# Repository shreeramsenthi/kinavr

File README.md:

kinavr
=======================================================================================

Hardware and firmware for automated approach to the recording of animal kinematics using inertial measurement units and AVR microcontrollers.

The schematics and board layouts for the modular data loggers can be found in the `board_design` subdirectory.
The source code for the firmware for data loggers make up the rest of the repository.

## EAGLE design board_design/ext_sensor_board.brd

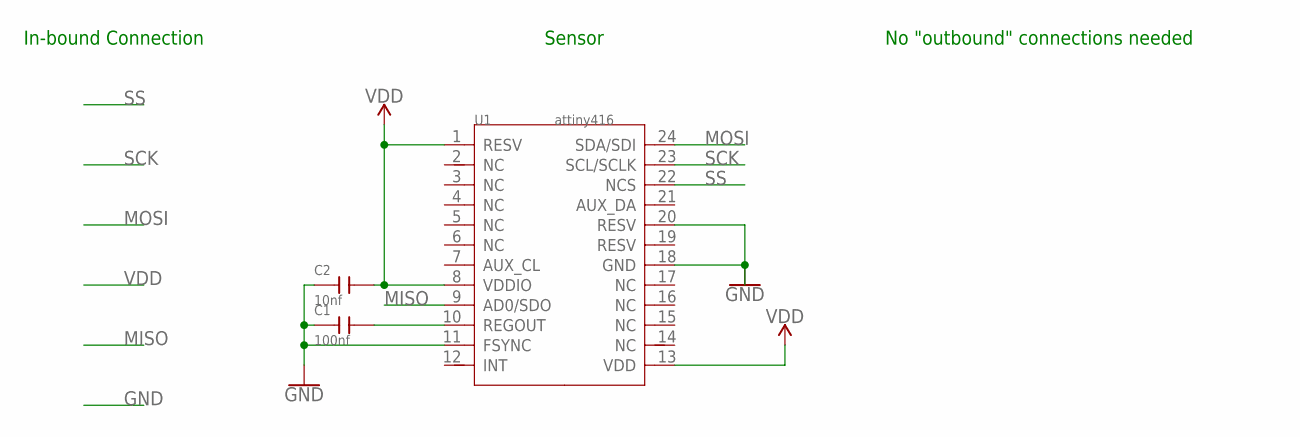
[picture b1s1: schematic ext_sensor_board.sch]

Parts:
C1: 100nf; C0402
C2: 10nf; C0402
U1: attiny416; QFN24G-0.4-3X3MM

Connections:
GND: C1.1, C2.1, U1.11 (FSYNC), U1.18 (GND), U1.20 (RESV)
MISO: U1.9 (AD0/SDO)
MOSI: U1.24 (SDA/SDI)
unnamed: C1.2, U1.10 (REGOUT)
SCK: U1.23 (SCL/SCLK)
SS: U1.22 (NCS)
VDD: C2.2, U1.1 (RESV), U1.8 (VDDIO), U1.13 (VDD)

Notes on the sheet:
Sensor
In-bound Connection
No "outbound" connections needed

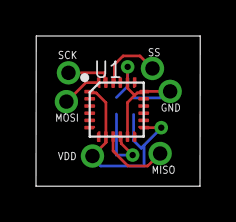
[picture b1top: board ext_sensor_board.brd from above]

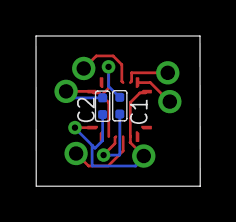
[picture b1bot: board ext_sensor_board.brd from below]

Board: 2 copper layers, 9.1 x 8.3 mm, 3 parts (2 on the bottom side), 3 nets.

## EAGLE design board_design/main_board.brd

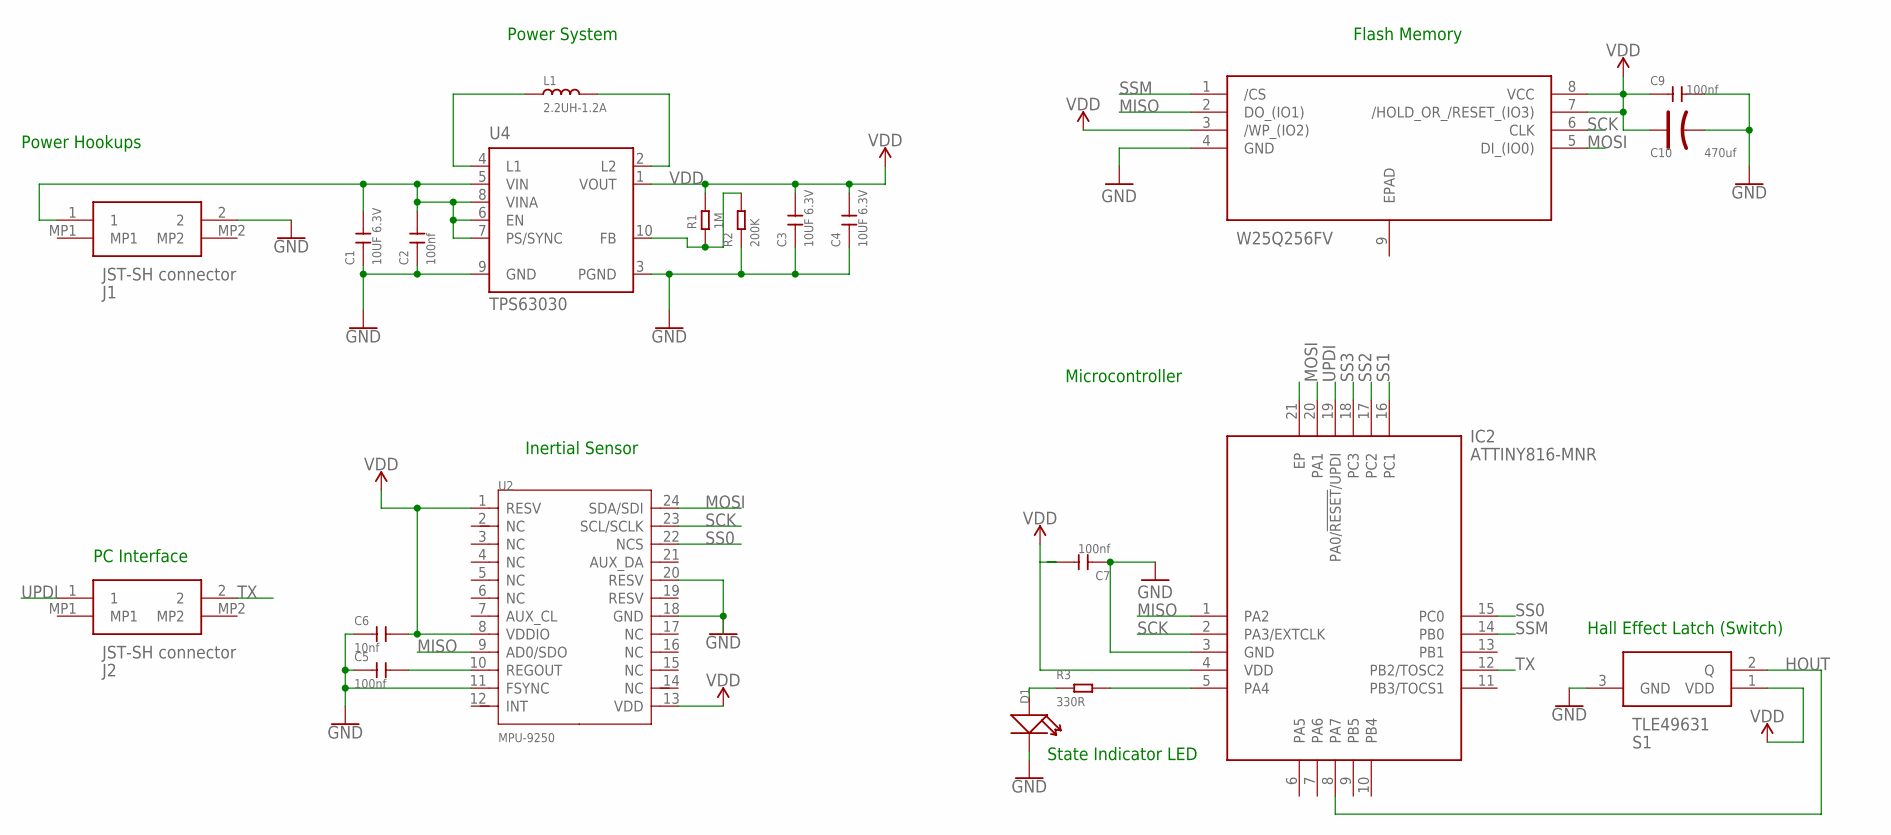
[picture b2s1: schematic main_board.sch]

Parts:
C1, C3, C4: 10UF 6.3V; C0603
C2, C7, C9: 100nf; C0603
C5: 100nf; C0402
C6: 10nf; C0402
C10: 470uf; AVX-D
D1: YELLOW-0603; LED-0603
IC1: W25Q256FV; SON127P800X600X80-9N
IC2: ATTINY816-MNR; QFN40P300X300X90-21N
J1, J2: JST-SH connector; BM02BSRSSTBLFSN
L1: 2.2UH-1.2A; L0805
R1: 1M; R0402
R2: 200K; R0603
R3: 330R; R0402
S1: TLE49631; SOT95P240X110-3N
U2: MPU-9250; QFN24G-0.4-3X3MM
U4: TPS63030; DRC-S-PVSON-N10

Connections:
GND: C1.1, C2.1, C3.1, C4.1, C5.1, C6.1, C7.1, C9.2, C10.-, D1.-, IC1.4 (GND), IC2.3 (GND), J1.2, R2.1, S1.3 (GND), U2.11 (FSYNC), U2.18 (GND), U2.20 (RESV), U4.3 (PGND), U4.9 (GND)
HOUT: IC2.8 (PA7), S1.2 (Q)
MISO: IC1.2 (DO_(IO1)), IC2.1 (PA2), U2.9 (AD0/SDO)
MOSI: IC1.5 (DI_(IO0)), IC2.20 (PA1), U2.24 (SDA/SDI)
unnamed: D1.+, R3.1
unnamed: L1.1, U4.4 (L1)
unnamed: L1.2, U4.2 (L2)
unnamed: R1.1, R2.2, U4.10 (FB)
unnamed: C1.2, C2.2, J1.1, U4.5 (VIN), U4.6 (EN), U4.7 (PS/SYNC), U4.8 (VINA)
unnamed: IC2.5 (PA4), R3.2
unnamed: C5.2, U2.10 (REGOUT)
SCK: IC1.6 (CLK), IC2.2 (PA3/EXTCLK), U2.23 (SCL/SCLK)
SS0: IC2.15 (PC0), U2.22 (NCS)
SS1: IC2.16 (PC1)
SS2: IC2.17 (PC2)
SS3: IC2.18 (PC3)
SSM: IC1.1 (/CS), IC2.14 (PB0)
TX: IC2.12 (PB2/TOSC2), J2.2
UPDI: IC2.19 (PA0/!RESET!/UPDI), J2.1
VDD: C3.2, C4.2, C6.2, C7.2, C9.1, C10.+, IC1.3 (/WP_(IO2)), IC1.7 (/HOLD_OR_/RESET_(IO3)), IC1.8 (VCC), IC2.4 (VDD), R1.2, S1.1 (VDD), U2.1 (RESV), U2.8 (VDDIO), U2.13 (VDD), U4.1 (VOUT)

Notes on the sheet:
Microcontroller
Power Hookups
PC Interface
Hall Effect Latch (Switch)
State Indicator LED
Power System
Flash Memory
Inertial Sensor

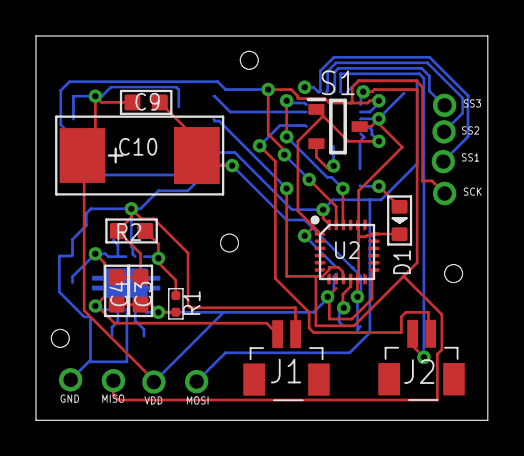
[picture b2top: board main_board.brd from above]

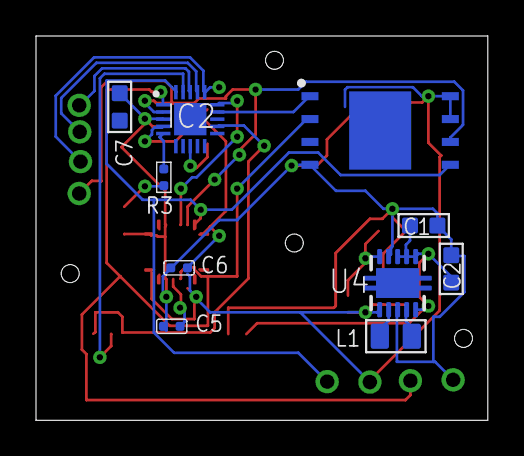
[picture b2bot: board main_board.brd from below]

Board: 2 copper layers, 25.1 x 21.4 mm, 21 parts (10 on the bottom side), 17 nets.

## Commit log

2019-07-30 Initial readme + gitignore
2019-07-30 Initialize main files in AS7
2019-07-30 Add timing code
2019-07-30 First build
2019-07-30 Add uart initialization
2019-07-30 Build previous
2019-07-30 More timer testing
2019-07-30 Build prev
2019-07-30 Add data output mode
2019-07-31 Test button ISR
2019-07-31 Test non-ISR buttons
2019-07-31 Remove testing lines from main, do
2019-07-31 Swap bit maps from int to uint8_t
2019-07-31 Minor SPI reorganization
2019-07-31 Add sensor tests
2019-07-31 Add sensor header file
2019-08-01 Add testing for writing samples to mem
2019-08-01 Fix typo in dc to wait for 2nd trigger
2019-08-02 Add testing for 20MHz clock
2019-08-03 Fix typos and build prev
2019-08-03 Initialize fuse setting
2019-08-03 Add source for fuse setting
2019-08-03 Add testing for 16MHz clock
2019-08-03 Switch all modes to 16MHz
2019-08-03 Time sampling code
2019-08-03 Test 500Hz sampling
2019-08-03 Test slower sampling
2019-08-03 Test 400Hz
2019-08-03 Test sample rate with bool flags
2019-08-03 Test that code catches multiple ISR calls
2019-08-03 Test that multiple ISRs halt code
2019-08-03 Test 500Hz with ISR flags
2019-08-03 Test 2kHz sampling
2019-08-03 Test 1kHz sampling
2019-08-03 Test 1.6kHz sampling
2019-08-03 Test address update in dc
2019-08-03 Test address update in dc, again
2019-08-03 More address testing
2019-08-03 Revert to working 1.6kHz sampling
2019-08-03 Test address update
2019-08-06 Fix math error in finding end of page
2019-08-06 Add testing for memory address fix
2019-08-06 Fix typo in address test
2019-08-06 Remove testing lines from dc
2019-08-06 Fix typo and build prev
2019-08-06 Convert mem addresses to uint32_t
2019-12-06 Add avrdude config file
2019-12-06 Add Makefile
2019-12-06 Adding solution file
2019-12-06 Add hex for polling sensor
2019-12-24 Test new mag switch
2019-12-24 Test blinking, 400Hz, and post-erase indication
2019-12-24 Test that sampling stops after one second
2019-12-24 Add break between x and z calibration
2019-12-25 Initial latch state is high, not low
2019-12-25 Better indication of modes and status
2019-12-25 Fix dc wait condition
2019-12-25 Stop timer more effectively
2019-12-25 Minor typo fix, indicate end of sampling
2019-12-25 Indicate end of output
2019-12-25 Remove hex file
2019-12-27 Modify dc to collect from two sensors at 200Hz
2019-12-27 Fix mixed indent in do
2019-12-27 Modify dc to collect data until battery dies
2020-03-02 800Hz, two stage cal, long mag breaks
    Modified for extracting flight stroke amplitude and plane angle.
    During collection, lights off mean something is being calibrated,
    erased, etc. Lights on indicate waiting for input or main behaviour.
2020-03-05 Switch to 1000dps and 8g sensitivity
2020-05-29 Add board designs

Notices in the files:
parts and their libraries:
SparkFun-Aesthetics: Licensing: Creative Commons ShareAlike 4.0 International - https://creativecommons.org/licenses/by-sa/4.0
